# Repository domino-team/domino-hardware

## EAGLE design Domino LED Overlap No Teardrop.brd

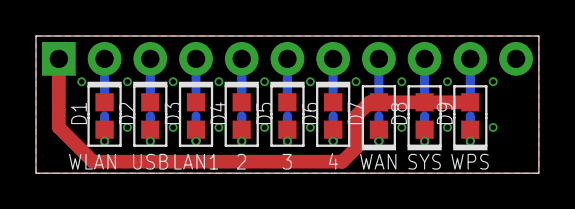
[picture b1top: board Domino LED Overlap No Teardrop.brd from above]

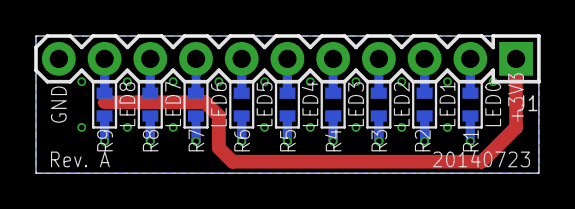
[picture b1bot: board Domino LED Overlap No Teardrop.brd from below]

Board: 2 copper layers, 27.9 x 7.6 mm, 23 parts (11 on the bottom side), 20 nets.

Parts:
CC-BY-SA1: CC-BY-SA_LOGO
D1: BLUE; LED0603
D2: WHITE; LED0603
D3, D4, D5, D6: GREEN; LED0603
D7: RED; LED0603
D8: ORANGE; LED0603
D9: YELLOW; LED0603
DRILEGEND: DRILEGEND
J1: MH11-1; MH11-1-0.1
R1, R2, R3, R4, R5, R6: 270R; R0603
R7, R8, R9: 330R; R0603
U$3: A5L-LOC
U$4: DOMINO_LOGO_SMALL

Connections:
+3V3: D7.2, D8.2, D9.2, J1.1
GND: D1.1, D2.1, D3.1, D4.1, D5.1, D6.1, J1.11
LED0: J1.2, R1.1
LED1: J1.3, R2.1
LED2: J1.4, R3.1
LED3: J1.5, R4.1
LED4: J1.6, R5.1
LED5: J1.7, R6.1
LED6: J1.8, R7.1
LED7: J1.9, R8.1
LED8: J1.10, R9.1
unnamed: D1.2, R1.2
unnamed: D2.2, R2.2
unnamed: D3.2, R3.2
unnamed: D4.2, R4.2
unnamed: D5.2, R5.2
unnamed: D7.1, R7.2
unnamed: D8.1, R8.2
unnamed: D9.1, R9.2
unnamed: D6.2, R6.2

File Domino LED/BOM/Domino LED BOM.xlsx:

Item | Qty | Value | Manufacturer | Device | Package | Reference | Description | Remarks
1 | 1 | BLUE | ANY | LED0603-BLUE | LED0603 | D1 | LED BLUE CLEAR 0603 SMD
2 | 1 | WHITE | ANY | LED0603-WHITE | LED0603 | D2 | LED WHITE CLEAR 0603 SMD
3 | 4 | GREEN | ANY | LED0603-GREEN | LED0603 | D3, D4, D5, D6 | LED GREEN CLEAR 0603 SMD
4 | 1 | RED | ANY | LED0603-RED | LED0603 | D7 | LED RED CLEAR 0603 SMD
5 | 1 | ORANGE | ANY | LED0603-ORANGE | LED0603 | D8 | LED ORANGE CLEAR 0603 SMD
6 | 1 | YELLOW | ANY | LED0603-YELLOW | LED0603 | D9 | LED YELLOW CLEAR 0603 SMD
7 | 1 | MH11-1 | ANY | MH11-1-0.1 | MH11-1-0.1 | J1 | CONN HEADER VERT .100 1ROW 11POS 8.08 HEAD 3.05 TAIL 15AU
8 | 6 | 270R | ANY | R0603_270R_5%_125mW | R0603 | R1, R2, R3, R4, R5, R6 | RES 270 OHM 1/8W 5% 0603 SMD
9 | 3 | 330R | ANY | R0603_330R_5%_125mW | R0603 | R7, R8, R9 | RES 330 OHM 1/8W 5% 0603 SMD

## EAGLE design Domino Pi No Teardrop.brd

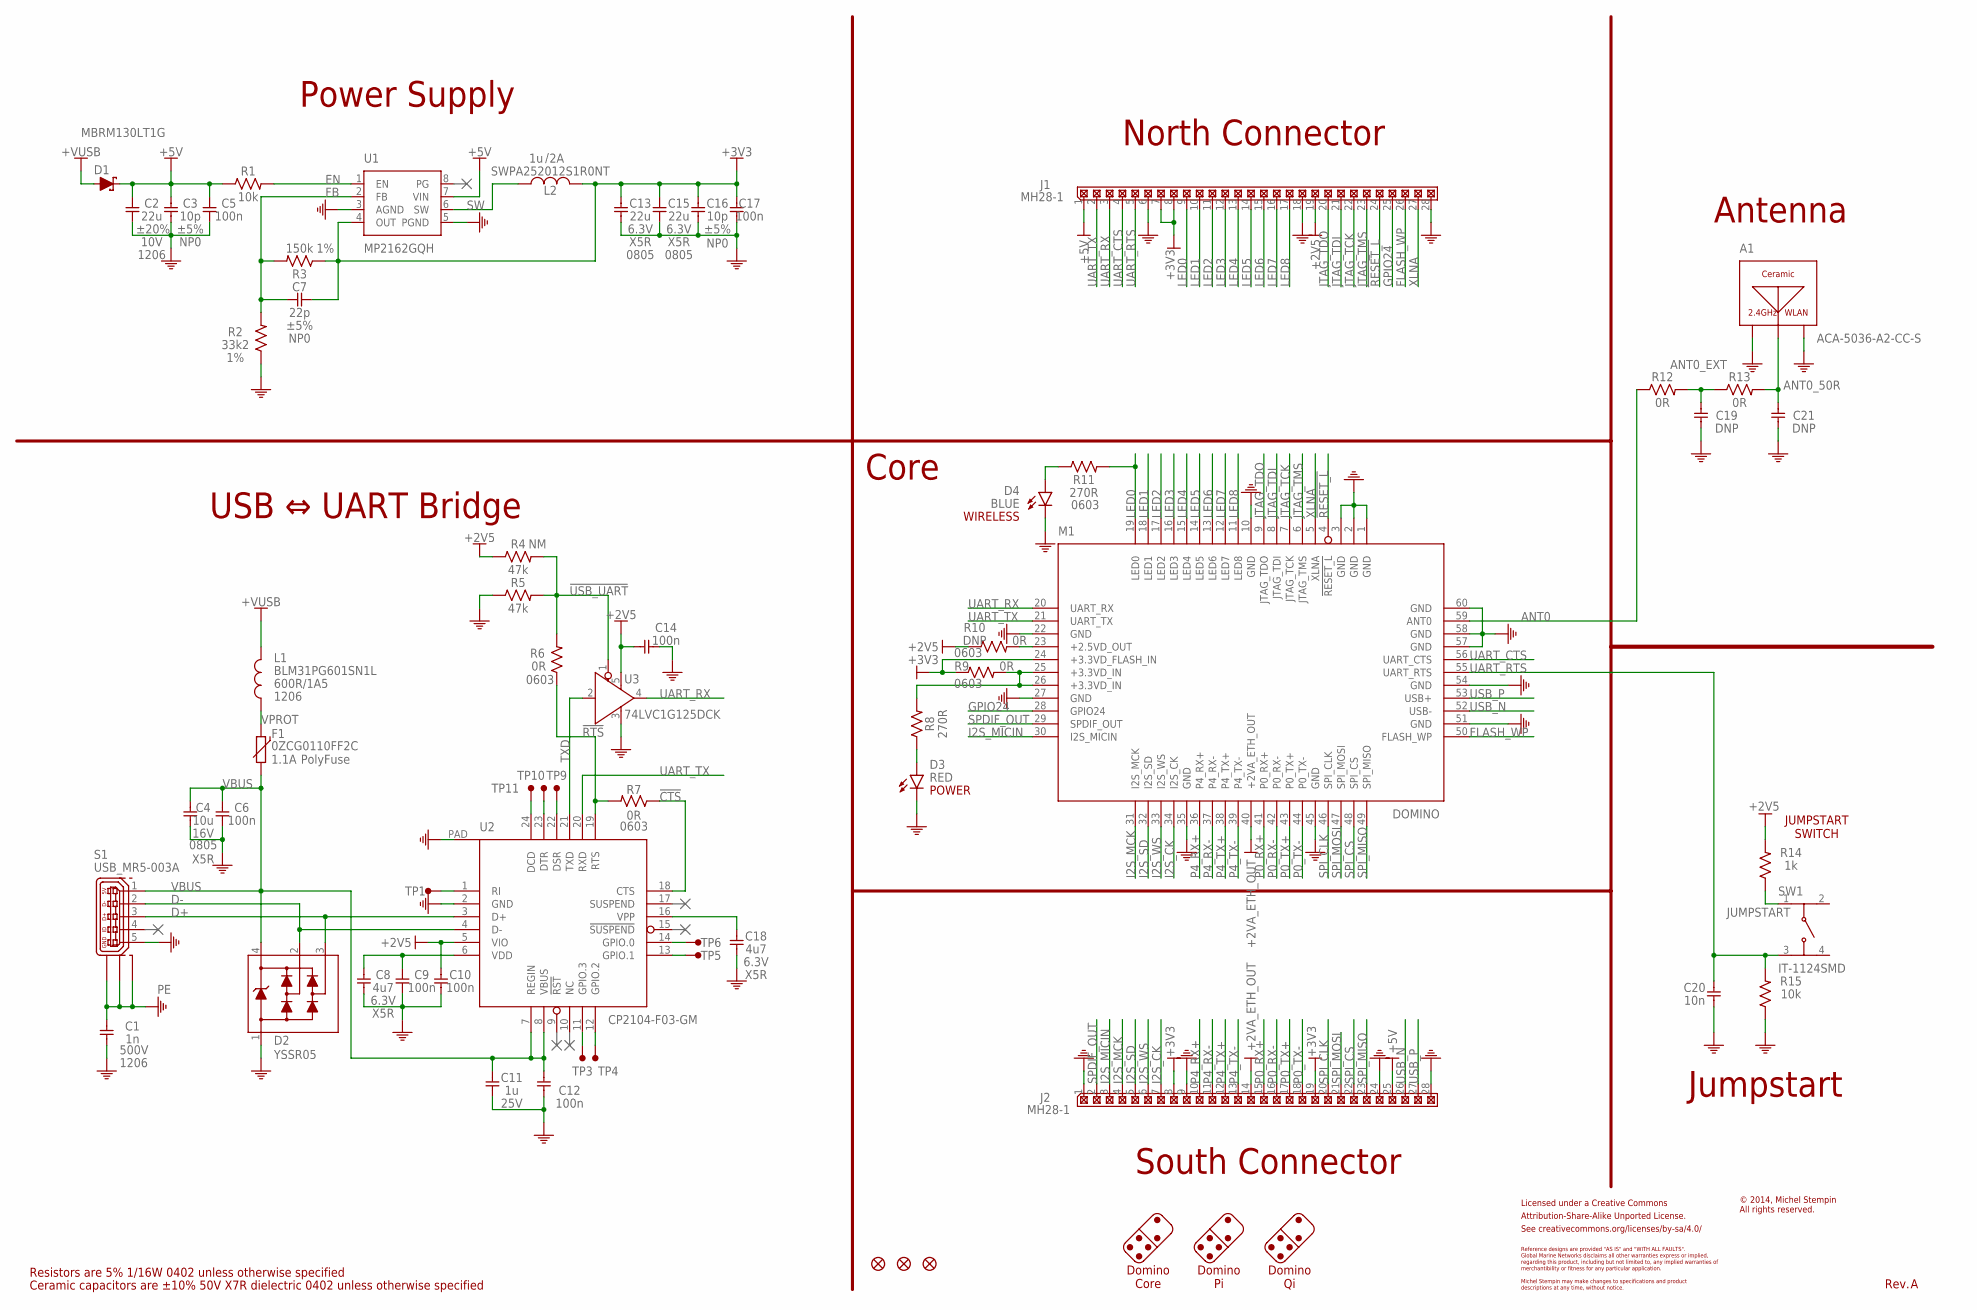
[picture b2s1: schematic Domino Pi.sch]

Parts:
A1: ACA-5036-A2-CC-S
C1: 1n; C1206; PARTNO C1206_1n_X7R_10%_CER_500V
C2: 22u; C1206; PARTNO C1206_22u_X7R_20%_CER_10V
C3, C16: 10p; C0402; PARTNO C0402_10p_NP0_5%_CER_50V
C4: 10u; C0805; PARTNO C0805_10u_X5R_10%_CER_16V
C5, C6, C9, C10, C12, C14, C17: 100n; C0402; PARTNO C0402_100n_X7R_10%_CER_50V
C7: 22p; C0402; PARTNO C0402_22p_NP0_5%_CER_50V
C8, C18: 4u7; C0402; PARTNO C0402_4u7_X5R_10%_CER_6V3
C11: 1u; C0402; PARTNO C0402_1u_X7R_10%_CER_25V
C13, C15: 22u; C0805; PARTNO C0805_22u_X5R_20%_CER_6V3
C19, C21: DNP; C0402; PARTNO C0402_DNP
C20: 10n; C0402; PARTNO C0402_10n_X7R_10%_CER_50V
CC-BY-SA: CC-BY-SA_LOGO
D1: MBRM130LT1G; DO-216AA; PARTNO MBRM130LT1G
D2: YSSR05; SOT143B; PARTNO YSSR05
D3: RED; LED0603; PARTNO LED0603-RED
D4: BLUE; LED0603; PARTNO LED0603-BLUE
F1: 0ZCG0110FF2C; PTC1812; PARTNO 0ZCG0110FF2C
F2, F3, F4: FIDUCIAL
J1, J2: MH28-1; MH28-1-0.1; PARTNO MH28-1-0.1
L1: BLM31PG601SN1L; FB1206; PARTNO BLM31PG601SN1L
L2: SWPA252012S1R0NT; SWPA252012S; PARTNO SWPA252012SMT
M1: DOMINO; PARTNO DOMINO-CORE
R1, R15: 10k; R0402; PARTNO R0402_10k_5%_62.5mW
R2: 33k2; R0402; PARTNO R0402_33k2_1%_62.5mW
R3: 150k; R0402; PARTNO R0402_150k_1%_62.5mW
R4, R5: 47k; R0402; PARTNO R0402_47k_5%_62.5mW
R6, R7, R9, R10: 0R; R0603; PARTNO R0603_0R_5%_125mW
R8: 270R; R0402; PARTNO R0402_270R_5%_62.5mW
R11: 270R; R0603; PARTNO R0603_270R_5%_125mW
R12, R13: 0R; R0402; PARTNO R0402_0R_5%_62.5mW
R14: 1k; R0402; PARTNO R0402_1k_5%_62.5mW
S1: USB_MR5-003A; PARTNO USB MR5-003A
SW1: IT-1124SMD; PARTNO IT-1124SMD
TP1, TP3, TP4, TP5, TP6, TP9, TP10, TP11: TEST_PAD
U1: MP2162GQH; QFN-8_2X1.5; PARTNO MP2162GQH
U2: CP2104-F03-GM; QFN-25_4X4; PARTNO CP2104-F03-GM
U3: 74LVC1G125DCK; SC70; PARTNO 74LVC1G125DCK

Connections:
!CTS: R7.1, U2.18 (CTS)
!RESET_L: J1.24, M1.4 (!RESET_L)
!RTS: R6.1, R7.2, U2.19 (RTS)
!USB_UART: R4.2, R5.2, R6.2, U3.1 (!OE)
+2.5VD_OUT: M1.23 (+2.5VD_OUT), R10.2
+2V5: C10.1, C14.2, J1.19, R4.1, R10.1, R14.2, U2.5 (VIO), U3.5 (VCC)
+2VA_ETH_OUT: J2.14, M1.40 (+2VA_ETH_OUT)
+3.3VD_IN: M1.25 (+3.3VD_IN), M1.26 (+3.3VD_IN), R8.2, R9.2
+3V3: C7.2, C13.1, C15.1, C16.1, C17.1, J1.7, J1.8, J2.8, J2.19, L2.2, M1.24 (+3.3VD_FLASH_IN), R3.1, R9.1, U1.4 (OUT)
+5V: C2.1, C3.1, C5.1, D1.1 (C), J1.1, J2.25, R1.1, U1.7 (VIN)
+VUSB: D1.2 (A), L1.1
ANT0: M1.59 (ANT0), R12.1
ANT0_50R: A1.FEED (A), C21.1, R13.2
ANT0_EXT: C19.1, R12.2, R13.1
BLUE_LED: D4.2 (A), R11.1
D+: D2.3, S1.3, U2.3 (D+)
D-: D2.2, S1.2, U2.4 (D-)
EN: R1.2, U1.1 (EN)
FB: C7.1, R2.2, R3.2, U1.2 (FB)
FLASH_WP: J1.26, M1.50 (FLASH_WP)
GND: A1.GND$1 (GND), A1.GND$2 (GND), C1.2, C2.2, C3.2, C4.2, C5.2, C6.2, C8.2, C9.2, C10.2, C11.2, C12.2, C13.2, C14.1, C15.2, C16.2, C17.2, C18.2, C19.2, C20.2, C21.2, D2.1, D3.1 (C), D4.1 (C), J1.6, J1.18, J1.28, J2.1, J2.9, J2.24, J2.28, M1.1 (GND), M1.2 (GND), M1.3 (GND), M1.10 (GND), M1.22 (GND), M1.27 (GND), M1.35 (GND), M1.45 (GND), M1.51 (GND), M1.54 (GND), M1.57 (GND), M1.58 (GND), M1.60 (GND), R2.1, R5.1, R15.1, S1.5, U1.3 (AGND), U1.5 (PGND), U2.2 (GND), U2.PAD, U3.3 (GND)
GPIO24: J1.25, M1.28 (GPIO24)
I2S_CK: J2.7, M1.34 (I2S_CK)
I2S_MCK: J2.4, M1.31 (I2S_MCK)
I2S_MICIN: J2.3, M1.30 (I2S_MICIN)
I2S_SD: J2.5, M1.32 (I2S_SD)
I2S_WS: J2.6, M1.33 (I2S_WS)
JTAG_TCK: J1.22, M1.7 (JTAG_TCK)
JTAG_TDI: J1.21, M1.8 (JTAG_TDI)
JTAG_TDO: J1.20, M1.9 (JTAG_TDO)
JTAG_TMS: J1.23, M1.6 (JTAG_TMS)
JUMPSTART: R14.1, SW1.1
LED0: J1.9, M1.19 (LED0), R11.2
LED1: J1.10, M1.18 (LED1)
LED2: J1.11, M1.17 (LED2)
LED3: J1.12, M1.16 (LED3)
LED4: J1.13, M1.15 (LED4)
LED5: J1.14, M1.14 (LED5)
LED6: J1.15, M1.13 (LED6)
LED7: J1.16, M1.12 (LED7)
LED8: J1.17, M1.11 (LED8)
unnamed: D3.2 (A), R8.1
unnamed: TP9.1, U2.22 (DSR)
unnamed: TP1.1, U2.1 (RI)
unnamed: TP3.1, U2.11 (GPIO.3)
unnamed: TP4.1, U2.12 (GPIO.2)
unnamed: TP10.1, U2.23 (DTR)
unnamed: TP11.1, U2.24 (DCD)
unnamed: TP6.1, U2.14 (GPIO.0)
unnamed: TP5.1, U2.13 (GPIO.1)
unnamed: C18.1, U2.16 (VPP)
P0_RX+: J2.15, M1.41 (P0_RX+)
P0_RX-: J2.16, M1.42 (P0_RX-)
P0_TX+: J2.17, M1.43 (P0_TX+)
P0_TX-: J2.18, M1.44 (P0_TX-)
P4_RX+: J2.10, M1.36 (P4_RX+)
P4_RX-: J2.11, M1.37 (P4_RX-)
P4_TX+: J2.12, M1.38 (P4_TX+)
P4_TX-: J2.13, M1.39 (P4_TX-)
PE: C1.1, S1.S$1 (M0), S1.S$2 (M1), S1.S$3 (M2)
SPDIF_OUT: J2.2, M1.29 (SPDIF_OUT)
SPI_CLK: J2.20, M1.46 (SPI_CLK)
SPI_CS: J2.22, M1.48 (SPI_CS)
SPI_MISO: J2.23, M1.49 (SPI_MISO)
SPI_MOSI: J2.21, M1.47 (SPI_MOSI)
SW: L2.1, U1.6 (SW)
TXD: U2.21 (TXD), U3.2 (A)
UART_CTS: J1.4, M1.56 (UART_CTS)
UART_RTS: C20.1, J1.5, M1.55 (UART_RTS), R15.2, SW1.3
UART_RX: J1.3, M1.20 (UART_RX), U3.4 (Y)
UART_TX: J1.2, M1.21 (UART_TX), U2.20 (RXD)
USB_N: J2.26, M1.52 (USB-)
USB_P: J2.27, M1.53 (USB+)
VBUS: C4.1, C6.1, C11.1, C12.1, D2.4, F1.2, S1.1, U2.7 (REGIN), U2.8 (VBUS)
VDD: C8.1, C9.1, U2.6 (VDD)
VPROT: F1.1, L1.2
XLNA: J1.27, M1.5 (XLNA)

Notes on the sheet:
PolyFuse
Power Supply
North Connector
South Connector
Antenna
Core
USB ⇔ UART Bridge
Ceramic capacitors are ±10% 50V X7R dielectric 0402 unless otherwise specified
Resistors are 5% 1/16W 0402 unless otherwise specified
Licensed under a Creative Commons
Attribution-Share-Alike Unported License.
See creativecommons.org/licenses/by-sa/4.0/
Reference designs are provided "AS IS" and "WITH ALL FAULTS".
regarding this product, including but not limited to, any implied warranties of
Michel Stempin may make changes to specifications and product
Global Marine Networks disclaims all other warranties express or implied,
merchantibility or fitness for any particular application.
descriptions at any time, without notice.
© 2014, Michel Stempin All rights reserved.
Rev.
Domino Core
Domino Pi
Domino Qi
WIRELESS
POWER
JUMPSTART SWITCH
Jumpstart

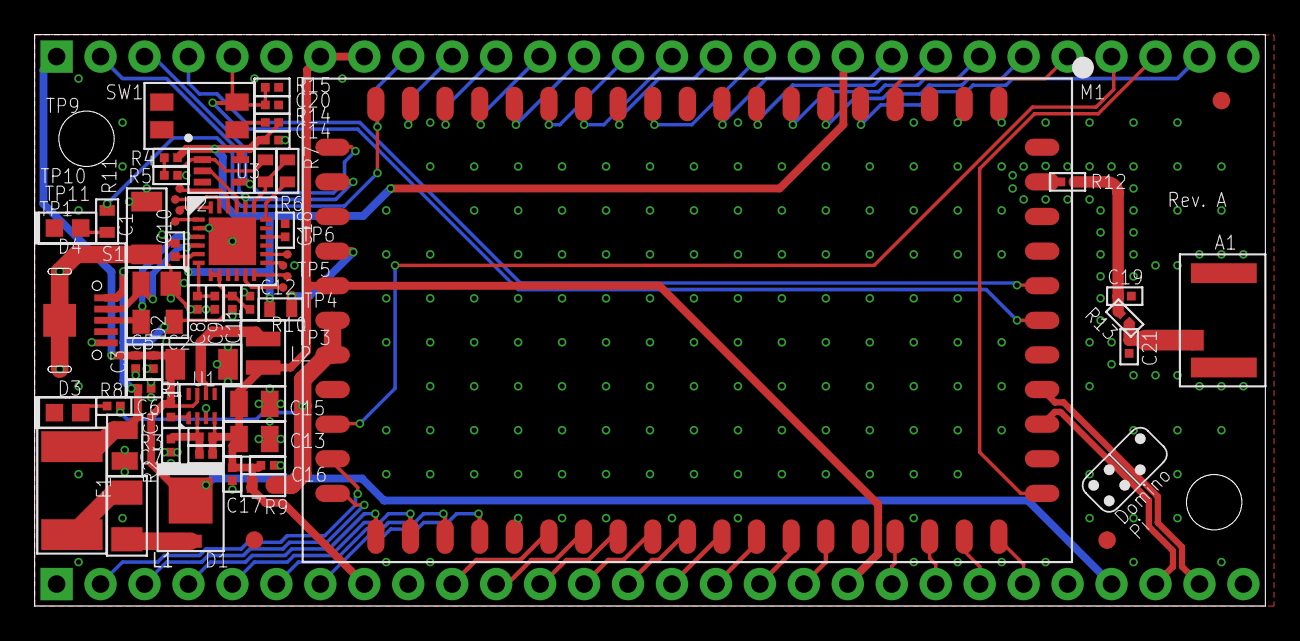
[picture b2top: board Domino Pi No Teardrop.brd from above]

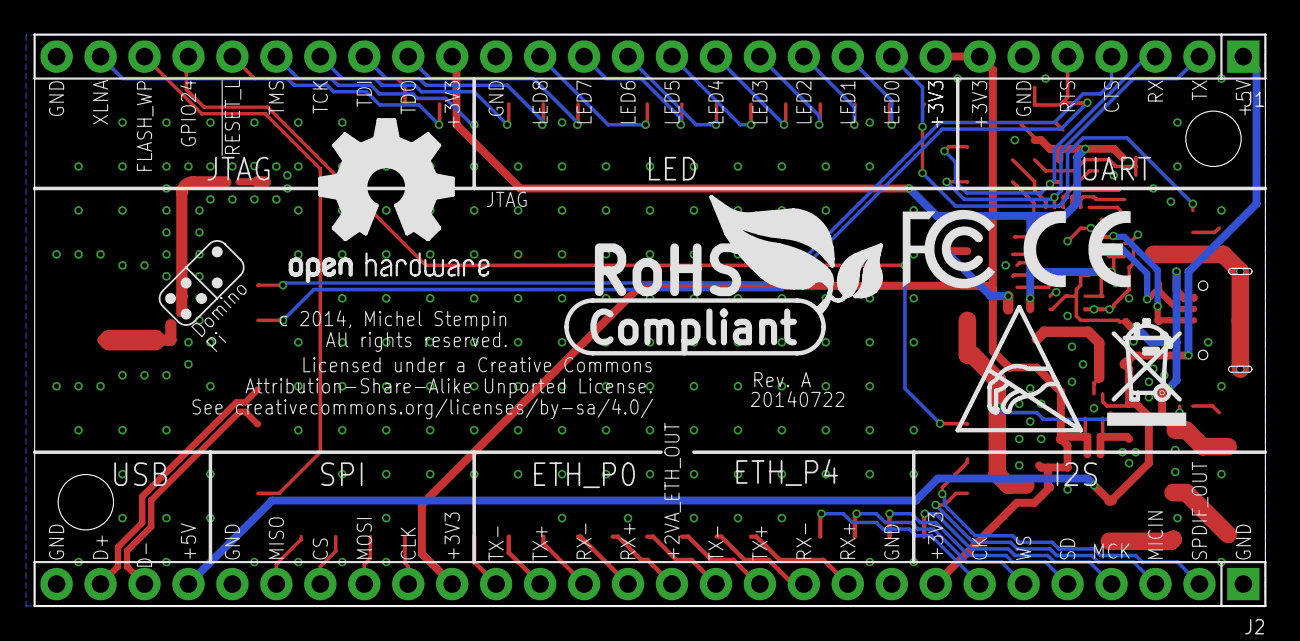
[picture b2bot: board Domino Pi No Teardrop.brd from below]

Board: 2 copper layers, 71.1 x 33.0 mm, 74 parts (9 on the bottom side), 77 nets.

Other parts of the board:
DRILEGEND: DRILEGEND
U$7, U$9: DOMINO_LOGO_SMALL
U$28: A5L-LOC
U$36: ESD_LOGO
U$38: OPEN_HARDWARE_LOGO
U$39: RECYCLE_BIN_LOGO
U$40: ROHS_LOGO
U$41: CE_LOGO_SMALL
U$42: FCC_LOGO_SMALL

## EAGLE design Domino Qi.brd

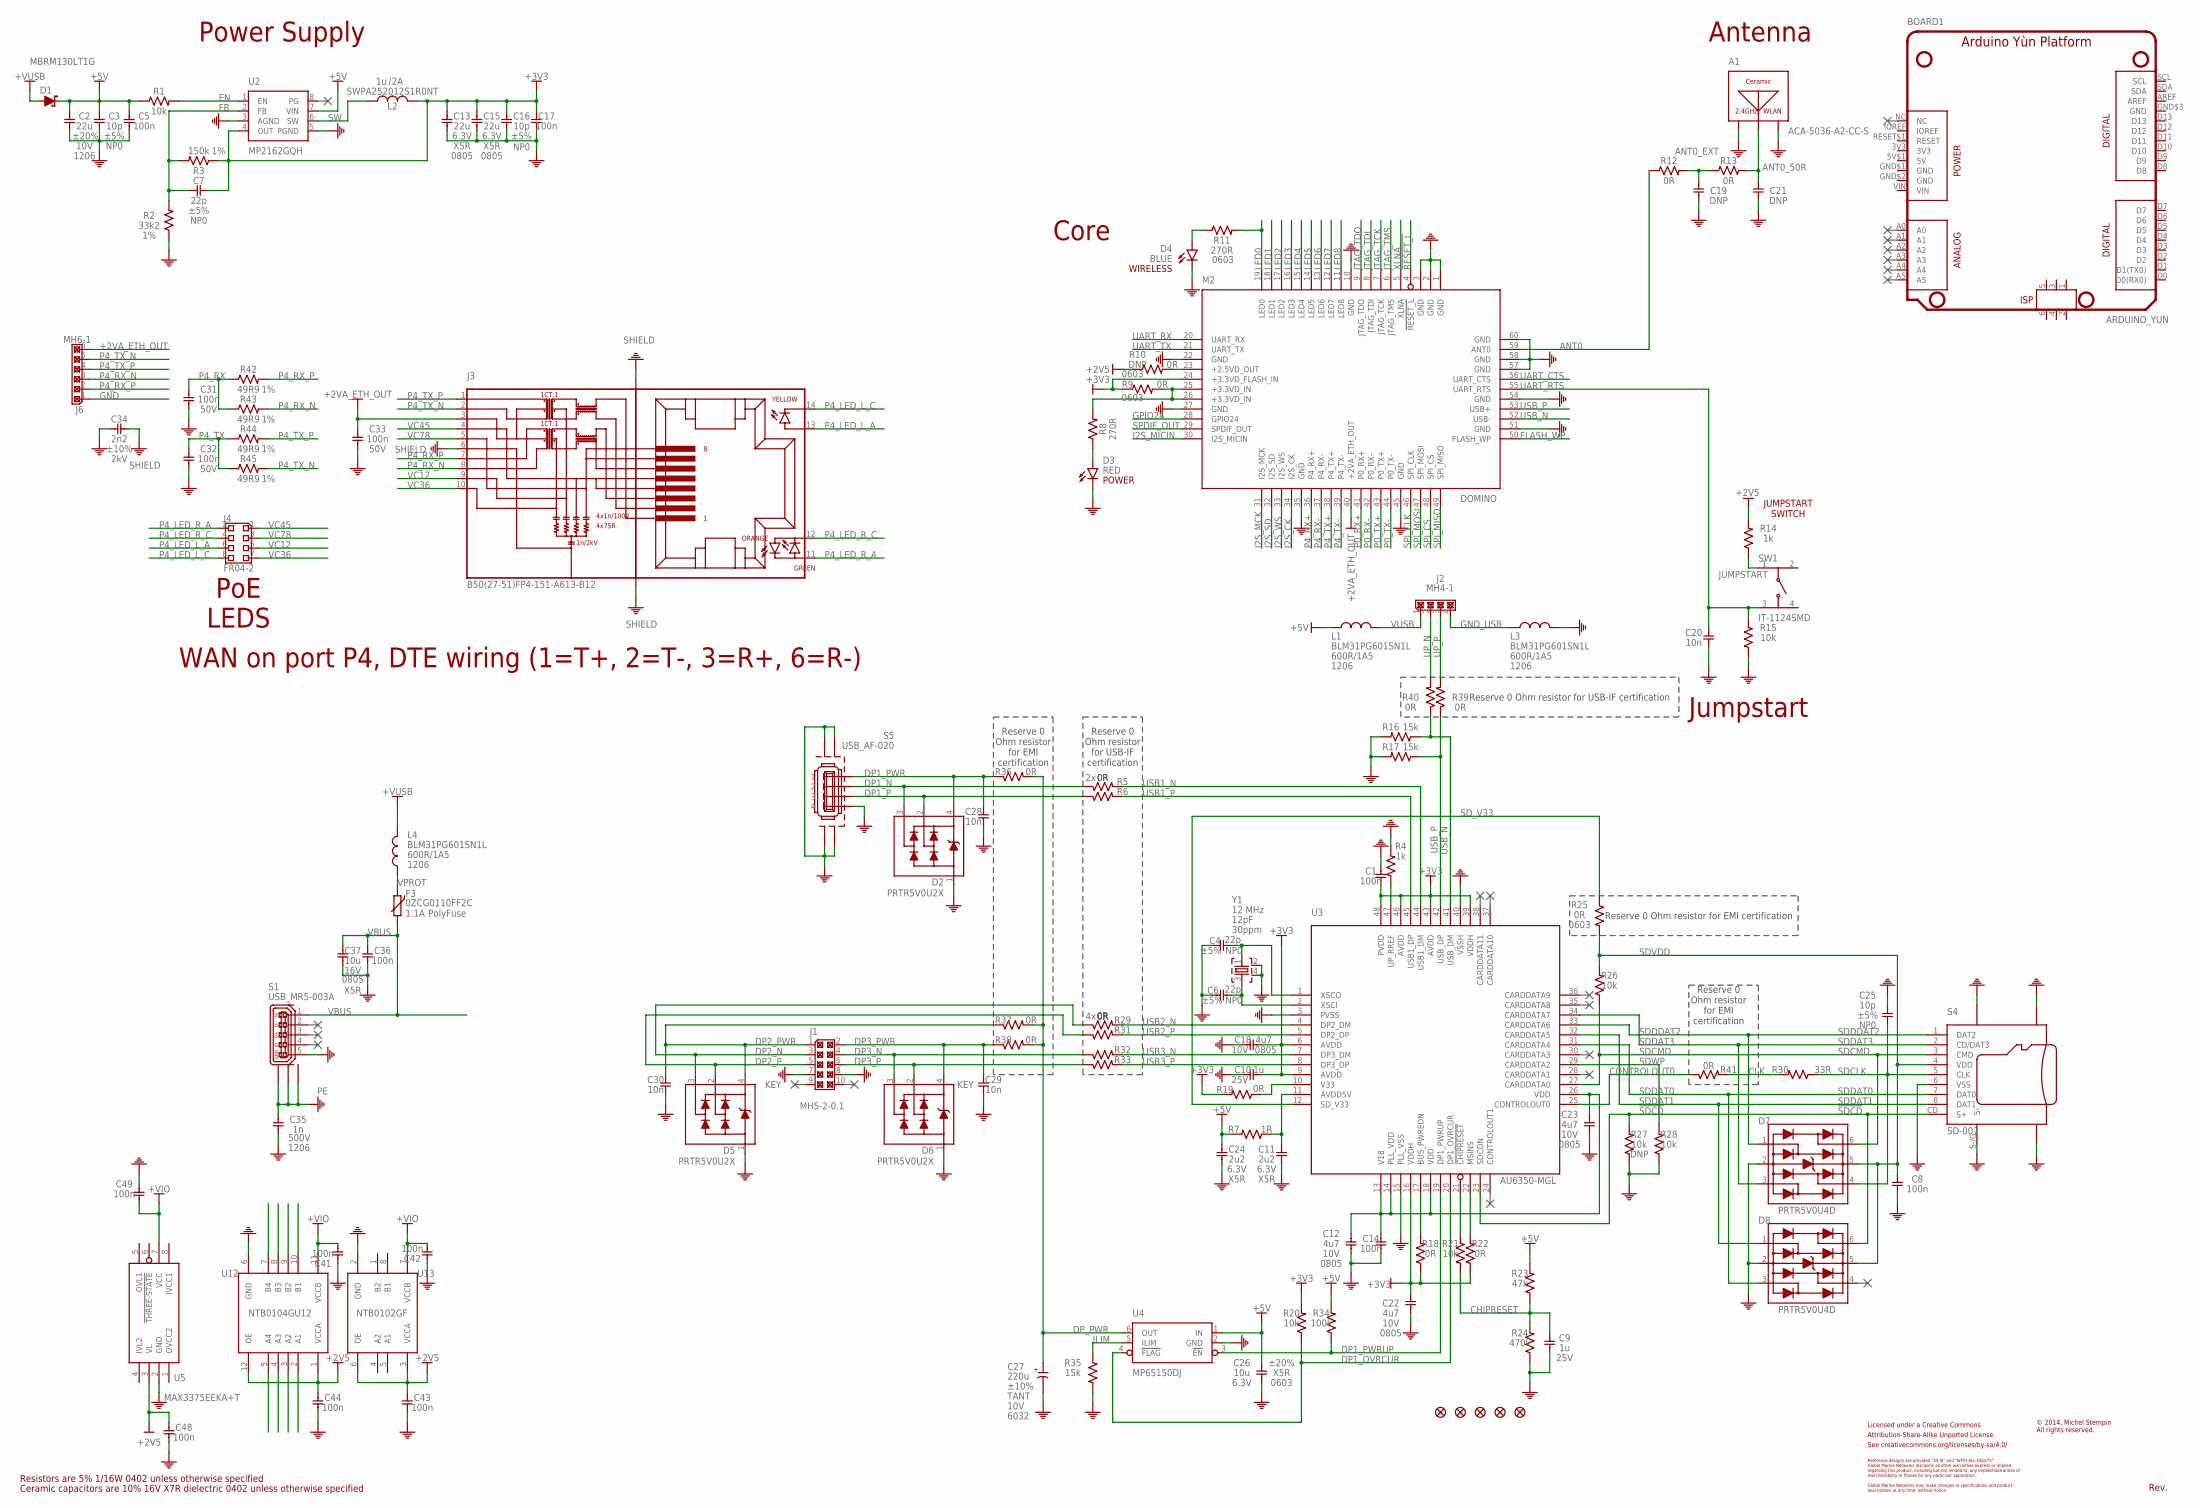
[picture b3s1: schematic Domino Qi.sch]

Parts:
A1: ACA-5036-A2-CC-S
BOARD1: ARDUINO_YUN; ARDUINO-YUN-PLATFORM
C1, C5, C8, C14, C17, C31, C32, C33, C36, C41, C42, C43, C44, C48, C49: 100n; C0402; PARTNO C0402_100n_X7R_10%_CER_50V
C2: 22u; C1206; PARTNO C1206_22u_X7R_20%_CER_10V
C3, C16, C25: 10p; C0402; PARTNO C0402_10p_NP0_5%_CER_50V
C4, C6, C7: 22p; C0402; PARTNO C0402_22p_NP0_5%_CER_50V
C9, C10: 1u; C0402; PARTNO C0402_1u_X7R_10%_CER_25V
C11, C24: 2u2; C0402; PARTNO C0402_2u2_X5R_10%_CER_6V3
C12, C18, C22, C23: 4u7; C0805; PARTNO C0805_4u7_X7R_10%_CER_6V3
C13, C15: 22u; C0805; PARTNO C0805_22u_X5R_20%_CER_6V3
C19, C21: DNP; C0402; PARTNO C0402_DNP
C20, C28, C29, C30: 10n; C0402; PARTNO C0402_10n_X7R_10%_CER_50V
C26: 10u; C0603; PARTNO C0603_10u_X5R_20%_CER_6V3
C27: 220u; C/6032-25; PARTNO CPOLC-6032_220u_20%_TANT_10V
C34: 2n2; C1206; PARTNO C1210_2n2_X7R_10%_CER_2kV
C35: 1n; C1206; PARTNO C1206_1n_X7R_10%_CER_500V
C37: 10u; C0805; PARTNO C0805_10u_X5R_10%_CER_16V
D1: MBRM130LT1G; DO-216AA; PARTNO MBRM130LT1G
D2, D5, D6: PRTR5V0U2X; SOT143B; PARTNO PRTR5V0U2X
D3: RED; LED0603; PARTNO LED0603-RED
D4: BLUE; LED0603; PARTNO LED0603-BLUE
D7, D8: PRTR5V0U4D; SOT23-6; PARTNO PRTR5V0U4D
F1, F2, F4, F5, F6: FIDUCIAL
F3: 0ZCG0110FF2C; PTC1812; PARTNO 0ZCG0110FF2C
J1: MH5-2-0.1; MH05-2-0.1; PARTNO MH5-2-0.1
J2: MH4-1; MH4-1-0.1; PARTNO MH4-1-0.1
J3: B50(27-51)FP4-151-A613-B12; PARTNO B50(27-51)FP4-151-A613-B12
J4: FR04-2; FR04-2-0.1; PARTNO FR04-2-0.1
J6: MH6-1; MH6-1-0.1; PARTNO MH6-1-0.1
L1, L3, L4: BLM31PG601SN1L; FB1206; PARTNO BLM31PG601SN1L
L2: SWPA252012S1R0NT; SWPA252012S; PARTNO SWPA252012SMT
M2: DOMINO; PARTNO DOMINO-CORE
R1, R15, R20, R21, R26, R27, R28: 10k; R0402; PARTNO R0402_10k_5%_62.5mW
R2: 33k2; R0402; PARTNO R0402_33k2_1%_62.5mW
R3: 150k; R0402; PARTNO R0402_150k_1%_62.5mW
R4, R14: 1k; R0402; PARTNO R0402_1k_5%_62.5mW
R5, R6, R12, R13, R18, R19, R22, R29, R31, R32, R33, R36, R37, R38, R39, R40, R41: 0R; R0402; PARTNO R0402_0R_5%_62.5mW
R7: 1R; R0402; PARTNO R0402_1R_5%_62.5mW
R8: 270R; R0402; PARTNO R0402_270R_5%_62.5mW
R9, R10, R25: 0R; R0603; PARTNO R0603_0R_5%_125mW
R11: 270R; R0603; PARTNO R0603_270R_5%_125mW
R16, R17, R35: 15k; R0402; PARTNO R0402_15k_5%_62.5mW
R23: 47k; R0402; PARTNO R0402_47k_5%_62.5mW
R24: 470k; R0402; PARTNO R0402_470k_5%_62.5mW
R30: 33R; R0402; PARTNO R0402_33R_5%_62.5mW
R34: 100k; R0402; PARTNO R0402_100k_5%_62.5mW
R42, R43, R44, R45: 49R9; R0402; PARTNO R0402_49R9_1%_62.5mW
S1: USB_MR5-003A; PARTNO USB MR5-003A
S4: SD-007; PARTNO SD-007
S5: USB_AF-020; PARTNO USB_AF-020
SW1: IT-1124SMD; PARTNO IT-1124SMD
U2: MP2162GQH; QFN-8_2X1.5; PARTNO MP2162GQH
U3: AU6350-MGL; LQFP-48_7X7; PARTNO AU6350-MGL
U4: MP65150DJ; SOT23-6; PARTNO MP65150DJ
U5: MAX3375EEKA+T; SOT23-8; PARTNO MAX3375EEKA+T
U12: NTB0104GU12; XQFN-12; PARTNO NTB0104GU12
U13: NTB0102GF; SOT1089; PARTNO NTB0102GF
U$2: CC-BY-SA_LOGO
Y1: 12 MHz; CRYSTAL_32X25; PARTNO CRYSTAL_32X25_2SH_12PF_30PPM

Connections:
5V: BOARD1.2 (5V), BOARD1.5V$1 (5V)
!CHIPRESET: R21.2, U3.21 (!CHIPRESET)
!RESET_L: M2.4 (!RESET_L)
!SDCD: D8.6 (I/O4), R27.2, S4.CD (S+), U3.23 (SDCDN)
+2.5VD_OUT: M2.23 (+2.5VD_OUT), R10.2
+2V5: C43.2, C44.2, C48.2, R10.1, R14.2, U5.3 (VL), U12.1 (VCCA), U12.12 (OE), U13.3 (VCCA), U13.6 (OE)
+2VA_ETH_OUT: C33.2, J3.3, J6.6, M2.40 (+2VA_ETH_OUT)
+3.3VD_IN1: M2.25 (+3.3VD_IN), M2.26 (+3.3VD_IN), R8.2, R9.2
+3V3: C1.2, C7.2, C10.2, C13.1, C15.1, C16.1, C17.1, C18.2, C22.2, L2.2, M2.24 (+3.3VD_FLASH_IN), R3.1, R9.1, R18.1, R19.2, R20.2, R22.1, U2.4 (OUT), U3.6 (AVDD), U3.9 (AVDD), U3.16 (VDDH), U3.39 (VDDH), U3.43 (AVDD), U3.46 (AVDD), U3.48 (PVDD)
+5V: C2.1, C3.1, C5.1, C24.1, C26.1, D1.1 (C), L1.2, R1.1, R7.2, R23.2, R34.2, U2.7 (VIN), U4.1 (IN)
+VIO: C41.1, C42.1, C49.1, U5.7 (VCC), U12.11 (VCCB), U13.7 (VCCB)
+VUSB: D1.2 (A), L4.1
ANT0: M2.59 (ANT0), R12.1
ANT0_50R: A1.FEED (A), C21.1, R13.2
ANT0_EXT: C19.1, R12.2, R13.1
AVDD5V1: C11.1, R7.1, U3.11 (AVDD5V)
BLUE_LED: D4.2 (A), R11.1
BUS_PWREDN: R18.2, U3.17 (BUS_PWREDN)
CHIPRESET: C9.1, R21.1, R23.1, R24.2
CLK: R30.2, R41.2
CONTROLOUT0: R41.1, U3.25 (CONTROLOUT0)
DP1_N: D2.3, R5.1, S5.2
DP1_OVRCUR: R20.1, U3.20 (DP1_OVRCUR), U4.4 (!FLAG)
DP1_P: D2.2, R6.1, S5.3
DP1_PWR: C28.1, D2.4, R36.1, S5.1
DP1_PWRUP: R34.1, U3.19 (DP1_PWRUP), U4.3 (!EN)
DP2_N: D5.3, J1.3, R29.1
DP2_P: D5.2, J1.5, R31.1
DP2_PWR: C30.1, D5.4, J1.1, R37.1
DP3_N: D6.3, J1.4, R32.1
DP3_P: D6.2, J1.6, R33.1
DP3_PWR: C29.1, D6.4, J1.2, R38.1
DP_PWR: C27.1 (+), R36.2, R37.2, R38.2, U4.6 (OUT)
EN: R1.2, U2.1 (EN)
FB: C7.1, R2.2, R3.2, U2.2 (FB)
FLASH_WP: M2.50 (FLASH_WP)
GND: A1.GND$1 (GND), A1.GND$2 (GND), BOARD1.6 (GND), BOARD1.GND$3 (GND), C1.1, C2.2, C3.2, C4.1, C5.2, C6.1, C8.2, C9.2, C10.1, C11.2, C12.1, C13.2, C14.2, C15.2, C16.2, C17.2, C18.1, C19.2, C20.2, C21.2, C22.1, C23.1, C24.2, C25.2, C26.2, C27.2 (-), C28.2, C29.2, C30.2, C31.1, C32.1, C33.1, C34.1, C35.2, C36.2, C37.2, C41.2, C42.2, C43.1, C44.1, C48.1, C49.2, D2.1, D3.1 (C), D4.1 (C), D5.1, D6.1, D7.2 (GND), D8.2 (GND), J1.7, J1.8, J6.1, L3.1, M2.1 (GND), M2.2 (GND), M2.3 (GND), M2.10 (GND), M2.22 (GND), M2.27 (GND), M2.35 (GND), M2.45 (GND), M2.51 (GND), M2.54 (GND), M2.57 (GND), M2.58 (GND), M2.60 (GND), R2.1, R4.2, R15.1, R16.2, R17.2, R24.1, R27.1, R28.1, R35.2, S1.5, S4.6 (VSS), S4.G$1 (G), S4.G$2 (G), S4.G$3 (G), S4.S-/G (S-), S5.4, S5.G$1 (G), S5.G$2 (G), S5.G$3 (G), S5.G$4 (G), U2.3 (AGND), U2.5 (PGND), U3.3 (PVSS), U3.15 (PLL_VSS), U3.40 (VSSH), U4.2 (GND), U5.2 (GND), U12.6 (GND), U13.2 (GND), Y1.2, Y1.4
GND_USB: J2.4, L3.2
GPIO24: M2.28 (GPIO24)
I2S_CK: M2.34 (I2S_CK)
I2S_MCK: M2.31 (I2S_MCK)
I2S_MICIN: M2.30 (I2S_MICIN)
I2S_SD: M2.32 (I2S_SD)
I2S_WS: M2.33 (I2S_WS)
ILIM: R35.1, U4.5 (ILIM)
IOREF: BOARD1.IOREF
JTAG_TCK: M2.7 (JTAG_TCK)
JTAG_TDI: M2.8 (JTAG_TDI)
JTAG_TDO: M2.9 (JTAG_TDO)
JTAG_TMS: M2.6 (JTAG_TMS)
JUMPSTART: R14.1, SW1.1
LED0: M2.19 (LED0), R11.2
LED1: M2.18 (LED1)
LED2: M2.17 (LED2)
LED3: M2.16 (LED3)
LED4: M2.15 (LED4)
LED5: M2.14 (LED5)
LED6: M2.13 (LED6)
LED7: M2.12 (LED7)
LED8: M2.11 (LED8)
MSINS: R22.2, U3.22 (MSINS)
unnamed: D3.2 (A), R8.1
P0_RX+: M2.41 (P0_RX+)
P0_RX-: M2.42 (P0_RX-)
P0_TX+: M2.43 (P0_TX+)
P0_TX-: M2.44 (P0_TX-)
P4_LED_L_A: J3.13, J4.6
P4_LED_L_C: J3.14, J4.8
P4_LED_R_A: J3.11, J4.2
P4_LED_R_C: J3.12, J4.4
P4_RX: C31.2, R42.1, R43.1
P4_RX+: M2.36 (P4_RX+)
P4_RX-: M2.37 (P4_RX-)
P4_RX_N: J3.8, J6.3, R43.2
P4_RX_P: J3.7, J6.2, R42.2
P4_TX: C32.2, R44.1, R45.1
P4_TX+: M2.38 (P4_TX+)
P4_TX-: M2.39 (P4_TX-)
P4_TX_N: J3.2, J6.5, R45.2
P4_TX_P: J3.1, J6.4, R44.2
PE: C35.1, S1.S$1 (M0), S1.S$2 (M1), S1.S$3 (M2)
SDCLK: C25.1, D7.4 (I/O3), R30.1, S4.5 (CLK)
SDCMD: D7.6 (I/O4), R26.1, S4.3 (CMD), U3.27 (CARDDATA0)
SDDAT0: D8.3 (I/O2), S4.7 (DAT0), U3.31 (CARDDATA4)
SDDAT1: D8.1 (I/O1), S4.8 (DAT1), U3.32 (CARDDATA5)
SDDAT3: D7.3 (I/O2), S4.2 (CD/DAT3), U3.34 (CARDDATA7)
SDDDAT2: D7.1 (I/O1), S4.1 (DAT2), U3.33 (CARDDATA6)
SDVDD: C8.1, D7.5 (VCC), D8.5 (VCC), R25.2, R26.2, S4.4 (VDD)
SDWP: R28.2, U3.29 (CARDDATA2)
SD_V33: R25.1, U3.12 (SD_V33)
SHIELD: C34.2, J3.6, J3.SH$1 (SHIELD), J3.SH$2 (SHIELD)
SPDIF_OUT: M2.29 (SPDIF_OUT)
SPI_CLK: M2.46 (SPI_CLK)
SPI_CS: M2.48 (SPI_CS)
SPI_MISO: M2.49 (SPI_MISO)
SPI_MOSI: M2.47 (SPI_MOSI)
SW: L2.1, U2.6 (SW)
UART_CTS: M2.56 (UART_CTS)
UART_RTS: C20.1, M2.55 (UART_RTS), R15.2, SW1.3
UART_RX: M2.20 (UART_RX)
UART_TX: M2.21 (UART_TX)
UP_N: J2.2, R40.2
UP_P: J2.3, R39.2
UP_PREF: R4.1, U3.47 (UP_RREF)
USB1_N: R5.2, U3.44 (USB1_DM)
USB1_P: R6.2, U3.45 (USB1_DP)
USB2_N: R29.2, U3.4 (DP2_DM)
USB2_P: R31.2, U3.5 (DP2_DP)
USB3_N: R32.2, U3.7 (DP3_DM)
USB3_P: R33.2, U3.8 (DP3_DP)
USB_N: M2.52 (USB-), R16.1, R40.1, U3.41 (USB_DM)
USB_P: M2.53 (USB+), R17.1, R39.1, U3.42 (USB_DP)
V1: R19.1, U3.10 (V33)
V18: C12.2, C14.1, C23.2, U3.13 (V18), U3.14 (PLL_VDD), U3.18 (VDD), U3.26 (VDD)
VBUS: C36.1, C37.1, F3.2, S1.1
VC12: J3.9, J4.5
VC36: J3.10, J4.7
VC45: J3.4, J4.1
VC78: J3.5, J4.3
VIN: BOARD1.VIN
VPROT: F3.1, L4.2
VUSB: J2.1, L1.1
XLNA: M2.5 (XLNA)
XSCI: C6.2, U3.2 (XSCI), Y1.3
XSCO: C4.2, U3.1 (XSCO), Y1.1

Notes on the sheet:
Ceramic capacitors are 10% 16V X7R dielectric 0402 unless otherwise specified
Resistors are 5% 1/16W 0402 unless otherwise specified
Licensed under a Creative Commons
Attribution-Share-Alike Unported License.
See creativecommons.org/licenses/by-sa/4.0/
Reference designs are provided "AS IS" and "WITH ALL FAULTS".
regarding this product, including but not limited to, any implied warranties of
Global Marine Networks may make changes to specifications and product
Global Marine Networks disclaims all other warranties express or implied,
merchantibility or fitness for any particular application.
descriptions at any time, without notice.
© 2014, Michel Stempin All rights reserved.
Rev.
Power Supply
Antenna
Core
WIRELESS
POWER
JUMPSTART SWITCH
Jumpstart
KEY
Reserve 0 Ohm resistor for EMI certification
Reserve 0 Ohm resistor for EMI certification
Reserve 0 Ohm resistor for USB-IF certification
Reserve 0 Ohm resistor for USB-IF certification
WAN on port P4, DTE wiring (1=T+, 2=T-, 3=R+, 6=R-)
LEDS
PoE
PolyFuse

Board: 2 copper layers, 128 parts (2 on the bottom side), 86 nets, no tracks yet.

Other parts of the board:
DRILEGEND: DRILEGEND
U$28: A5L-LOC

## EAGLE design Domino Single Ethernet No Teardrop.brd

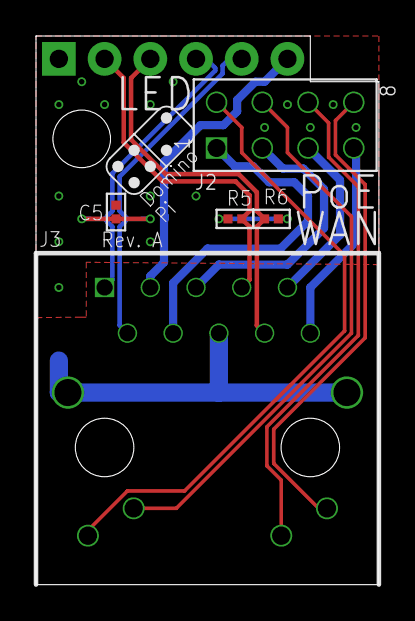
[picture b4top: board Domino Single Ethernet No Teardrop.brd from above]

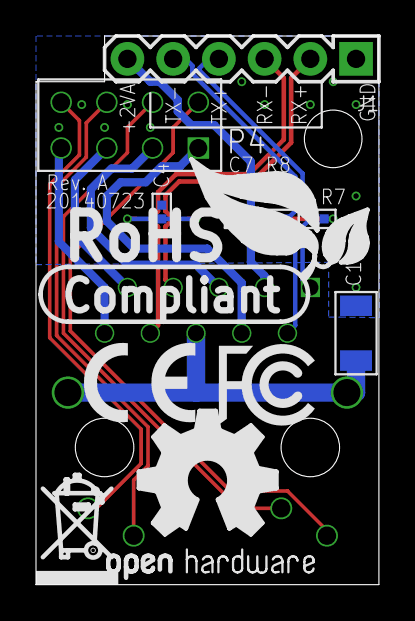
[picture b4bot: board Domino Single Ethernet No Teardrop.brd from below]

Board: 2 copper layers, 19.1 x 30.5 mm, 20 parts (11 on the bottom side), 17 nets.

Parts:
C1: 2n2; C1206
C4, C5, C7: 100n; C0402
CC-BY-SA1: CC-BY-SA_LOGO
DRILEGEND: DRILEGEND
J1: MH6-1; MH6-1-0.1
J2: FR04-2; FR04-2-0.1
J3: B50(27-51)FP4-151-A613-B12
R5, R6, R7, R8: 49R9; R0402
U$3: A5L-LOC
U$4: DOMINO_LOGO_SMALL
U$5: CE_LOGO_SMALL
U$6: FCC_LOGO_SMALL
U$7: OPEN_HARDWARE_LOGO
U$8: RECYCLE_BIN_LOGO
U$9: ROHS_LOGO

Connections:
+2VA_ETH_OUT: C7.2, J1.6, J3.3
GND: C1.1, C4.1, C5.1, C7.1, J1.1
P4_LED_L_A: J2.6, J3.13
P4_LED_L_C: J2.8, J3.14
P4_LED_R_A: J2.2, J3.11
P4_LED_R_C: J2.4, J3.12
P4_RX: C4.2, R5.1, R6.1
P4_RX_N: J1.3, J3.8, R6.2
P4_RX_P: J1.2, J3.7, R5.2
P4_TX: C5.2, R7.1, R8.1
P4_TX_N: J1.5, J3.2, R8.2
P4_TX_P: J1.4, J3.1, R7.2
SHIELD: C1.2, J3.6, J3.SH$1, J3.SH$2
VC12: J2.5, J3.9
VC36: J2.7, J3.10
VC45: J2.1, J3.4
VC78: J2.3, J3.5

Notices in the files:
Domino Qi/Domino Qi.sch:
© 2014, The Domino Team
All rights reserved.
parts and their libraries:
Domino: See creativecommons.org/licenses/by-sa/4.0/ for details.
Domino: See creativecommons.org/licenses/by-sa/3.0/ for details.
Domino: Copyright © 2012, Michel Stempin, All rights reserved
Licenced under Creative Commons CC BY-SA 3.0 license.
